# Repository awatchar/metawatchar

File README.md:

# metawatchar

Research repository for a PhD project on **electromagnetic metamaterials at RF frequencies**.

**Author:** Watchara Amasiri, Department of Electrical and Computer Engineering, Thammasat University

> Status: early stage, work in progress. Content will be added as the research progresses.

## Approach

The work combines simulation, fabrication, and measurement:

1. **Design and simulate** structures with open-source full-wave electromagnetic solvers, using an HPC cluster for parameter sweeps and optimization.
2. **Fabricate** prototypes as printed circuit boards.
3. **Measure** prototypes with RF instruments (vector network analysis, and free-space measurement in an anechoic chamber).
4. **Compare** measured and simulated results.

## Repository layout

| Path | Contents |
|---|---|
| `sim/<case>/` | Simulation scripts, job files, and summarized results (e.g., S-parameters, figures) for each case |

Large raw outputs, such as 3-D field dumps, are not stored in this repository.

## Reproducibility

Each case folder will describe the solver and version, the input parameters, and how to regenerate its results.

## License

- **Code** (scripts, simulation models, job files) is licensed under the [MIT License](LICENSE).
- **Data and results** (measured and simulated data, figures, and documentation) are licensed under [Creative Commons Attribution 4.0 International (CC BY 4.0)](LICENSE-CC-BY-4.0).

If you use this work, please cite the related publications (to be listed here) and credit Watchara Amasiri.

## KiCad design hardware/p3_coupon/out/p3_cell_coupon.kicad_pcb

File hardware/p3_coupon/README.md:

# P3 coupons and test fixtures (v1)

Boards for characterising the lumped LC cells of the 85 kHz magnetic metamaterial slab (study P3) before the slab itself is designed. All boards are generated by scripts (KiCad 10 Python) and checked by DRC: 0 errors, 0 warnings, no unconnected items.

| Board | Script | Size | Stack | Assembly | Purpose |
|---|---|---|---|---|---|
| `p3_cell_coupon` | `coupon_cells.py` | 225 × 210 mm | 2-layer, 1 oz | JLCPCB PCBA (81 parts) | Isolated cells (f0, Q, spread), coplanar pairs, L-only controls |
| `p3_array_coupon` | `coupon_arrays.py` | 270 × 185 mm | 2-layer, **2 oz** | JLCPCB PCBA (100 parts) + 1 hand-soldered SMA | 4 × 4 mini-arrays per cell type; printed-spiral reference cells |
| `p3_ztab` | `small_boards.py` | 11 × 52 mm | 2-layer, 1 oz | hand | One drum inductor + edge SMA: L, ESR, Q and Z21 vs distance (m_eff) |
| `p3_probe10`, `p3_probe20` | `small_boards.py` | 12 / 22 × 85 mm | **4-layer** | hand (SMA) | Shielded H-field loop probes, loop OD 10 / 20 mm |
| `p3_helmholtz` | `small_boards.py` | 110 × 110 mm | 2-layer, **2 oz** | hand (2 wires) | One coil of a Helmholtz pair for probe calibration |

Shared code: `p3pcb.py` (builder, cell types, spiral, export chain). Custom footprints: `footprints.pretty/`. Outputs: `out/` (boards, renders, DRC reports, cell maps) and `out/jlc_<board>/` (Gerber zip, BOM and CPL for JLCPCB).

## Cell types

Each cell is a closed loop: one unshielded ferrite drum inductor (axis normal to the board) and a C0G capacitor.

| Type | Inductor (LCSC) | Capacitor (LCSC) | Nominal f0 |
|---|---|---|---|
| A | Sumida CD105T125NP-470KC, 47 µH ±10 %, Ø10.4 mm (C171573) | Murata GRM3195C1H683JA05D, 68 nF C0G 1206 (C3847777) | 89.1 kHz |
| B | SXN SM7850-101MT, 100 µH ±20 %, Ø7.8 mm (C10155) | TDK C2012C0G1H333JT000N, 33 nF C0G 0805 (C76628) | 87.6 kHz |
| C | Bourns SDR0805-101KL, 100 µH ±10 %, Ø7.8 mm (C139487) | TDK C2012C0G1H333JT000N, 33 nF C0G 0805 (C76628) | 87.6 kHz |

Inductor footprints follow the manufacturers' recommended land patterns (Sumida CD105/T125 Ver. 2021-03-05; SXN SM series p. 2; Bourns SDR0805). The Z-tab uses one universal land that covers all three. The 3D bodies reuse KiCad's SDR1806 model scaled to size, for visualisation only.

## Board 1: cell coupon

- **Isolated cells A1–A7, B1–B7, C1–C7** at 30 mm pitch (neighbour coupling k ≲ 10⁻³, below 1/Q). Each has a DNP pad for a parallel trim capacitor.
- **Pairs xP11.5, xP14, xP18** (x = A, B, C): coplanar cells at 11.5, 14 and 18 mm centre spacing. The pair splits into two modes, and k = (f+² − f−²)/(f+² + f−²) where the splitting exceeds the linewidth. For coplanar cells k < 0.
- **AL, BL, CL**: inductor without a capacitor (the non-resonant control).
- Four M3 holes locate the 3D-printed probe jig. Cell coordinates are in `out/p3_cell_coupon_map.json`.

## Board 2: mini-arrays and printed reference cells

- **4 × 4 arrays**: type A at 15 mm pitch, B and C at 12.5 mm. The capacitor sits in the gap beside each inductor; there are no trim pads. These show the collective (uniform) mode of a small lattice, which is checked against the full mutual-inductance model.
- **S1, S2**: printed square spiral, 38 mm, 17 turns, 0.6 mm trace with 0.25 mm gap, top layer, bottom-layer crossover. L ≈ 7.7 µH (modified Wheeler), with 2 × 220 nF C0G (Murata GRM31C5C1H224JE02L, C464977) giving 86.7 kHz nominal, plus a DNP trim pad. Q is only about 6 at most, even with 2 oz copper. This is the exactly modelled reference cell, not a performance cell.
- **SZ**: the same spiral with no capacitor, wired to an edge SMA (J1, hand-soldered) for a direct measurement of L and R.

## Small boards

- **Z-tab**: the inductor sits at the tip (11 mm wide, so two tabs side by side reach 11.5 mm centre spacing) and the edge SMA at the far end. The feed is a top/bottom broadside pair, which keeps the lead loop small.
  - One tab gives L, ESR and Q.
  - Two tabs on the jig give Z21 = jωM against distance, which is fitted to M = μ0 m_eff² / (4π d³) for the coplanar case (and the coaxial case if stacked).
  - Order 10.
- **Loop probes**: two turns on each inner layer (four in series, OD 10 or 20 mm). Both outer layers are a ground shield, slit from the loop centre to the tip, so H passes, E is blocked, and the shield forms no shorted turn. Stitching vias run along the stem. The loop meets ground only at the connector, through a net tie.
  - The pair is used weakly coupled for cell f0/Q, and singly for field maps.
- **Helmholtz coil**: a 10-turn circular spiral, r = 46 → 34 mm (mean 40 mm). Two boards go on 40 mm spacers with the coils in series. The calibration field is computed from the actual track geometry (Biot–Savart), not from the ideal-loop formula.

## Ordering (one batch)

| Board | Qty | Options |
|---|---|---|
| Cell coupon | 5 PCB, 2 assembled | FR-4 1.6 mm, 1 oz, ENIG (flat lands for the large inductors), PCBA top side |
| Array coupon | 5 PCB, 2 assembled | FR-4 1.6 mm, **2 oz**, ENIG, PCBA top side |
| Z-tab | 10 | FR-4 1.6 mm, 1 oz |
| Probe 10, Probe 20 | 5 each | **4-layer**, 1.6 mm, standard stack-up |
| Helmholtz | 5 (2 needed) | FR-4 1.6 mm, **2 oz** |

**Loose parts for hand assembly:**
- Drum inductors of each type for the Z-tabs (about 4 of each).
- Edge-mount SMA jacks for 1.6 mm boards: 4 for the probes, 1 for SZ, and up to 10 for Z-tabs. The footprint is Samtec SMA-J-P-H-ST-EM1. Check that any generic edge SMA you buy matches its pads (centre 1.27 × 3.2 mm; grounds at ±2.825 mm, top and bottom).
- M3 nylon spacers, 40 mm, for the Helmholtz pair.

**Check in the JLCPCB DFM preview before paying:**
- Inductor rotation: both pads must lie along the board's y axis.
- The SDR0805 pad gap is read from the datasheet figure as 2.4 mm. Compare it with the library footprint of C139487.
- On the array coupon, the capacitor positions between the inductors.

## Regenerate

```bash
"C:/Program Files/KiCad/10.0/bin/python.exe" coupon_cells.py
```

Run `coupon_arrays.py` and `small_boards.py` the same way. Each script saves the board and then runs DRC, the Gerber/drill/position exports, the JLCPCB BOM/CPL and the renders.

## Not included yet

- The 3D-printed probe jig.
- TX/RX WPT coils and the slab itself. These are designed after the coupon data (cell Q, m_eff and spread) are measured.

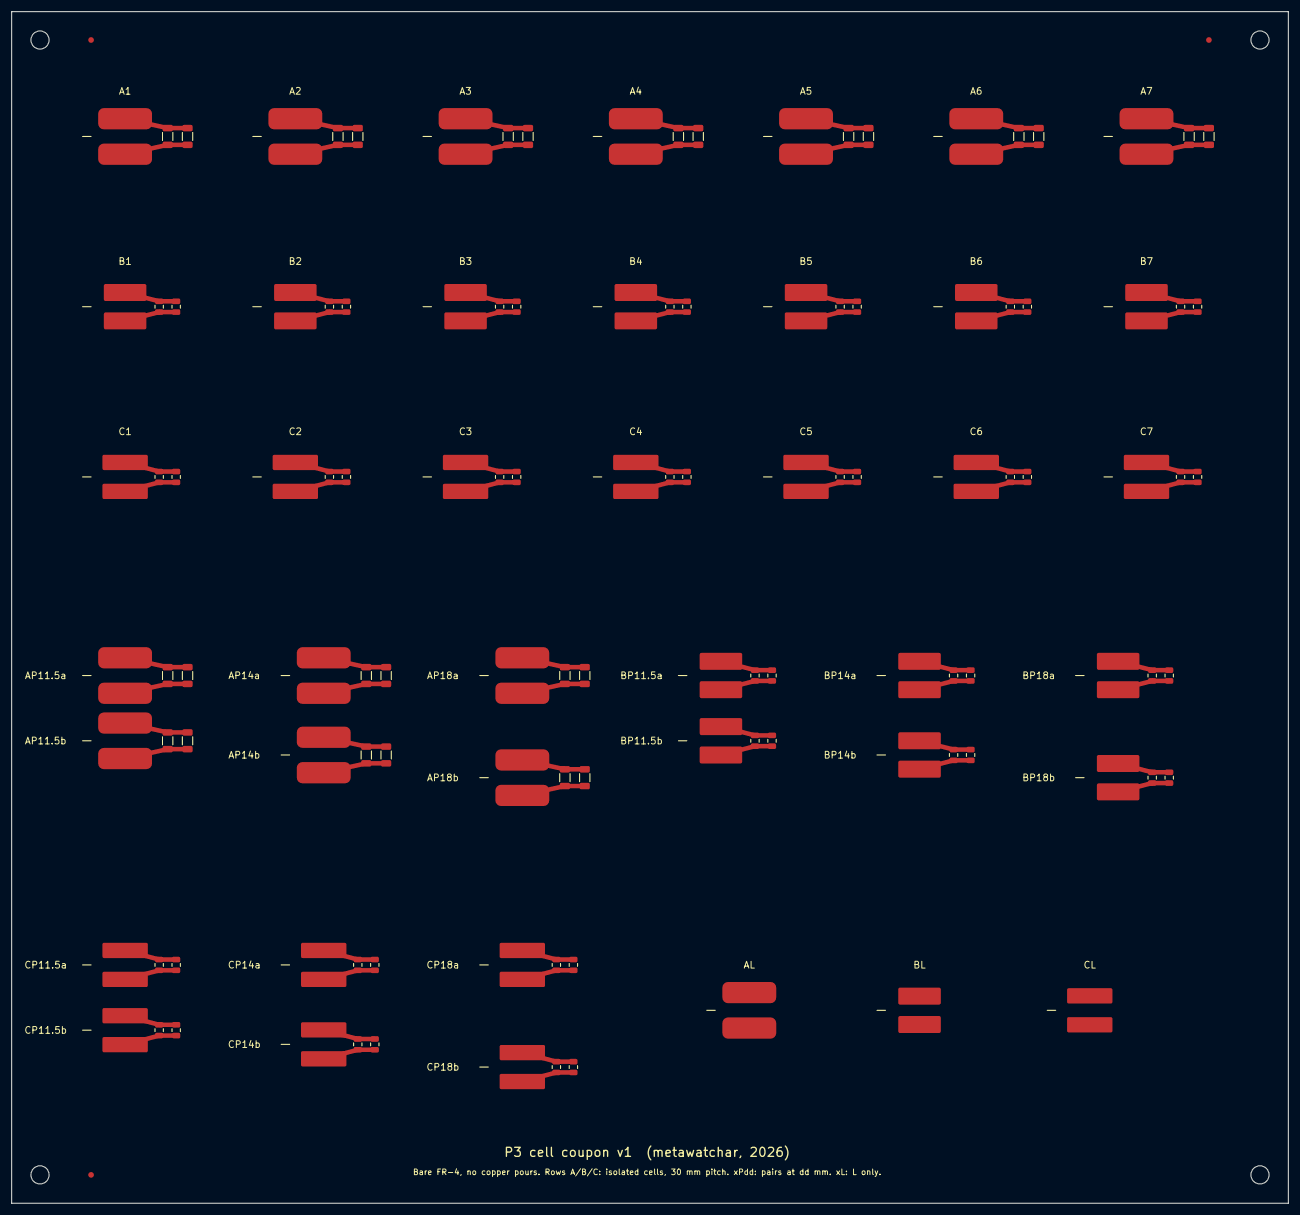
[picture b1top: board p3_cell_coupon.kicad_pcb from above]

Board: 2 copper layers, 225.0 x 210.0 mm, 127 parts (0 on the bottom side), 78 nets.

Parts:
C1, C3, C5, C7, C9, C11, C13, C43, C45, C47, C49, C51, C53: 68nF C0G; C_1206_3216Metric
C2, C4, C6, C8, C10, C12, C14, C44, C46, C48, C50, C52, C54: DNP trim; C_1206_3216Metric
C15, C17, C19, C21, C23, C25, C27, C29, C31, C33, C35, C37, C39, C41, C55, C57, C59, C61, C63, C65, C67, C69, C71, C73, C75, C77: 33nF C0G; C_0805_2012Metric
C16, C18, C20, C22, C24, C26, C28, C30, C32, C34, C36, C38, C40, C42, C56, C58, C60, C62, C64, C66, C68, C70, C72, C74, C76, C78: DNP trim; C_0805_2012Metric
FID1, FID2, FID3: Fiducial; Fiducial_1mm_Mask2mm
H1, H2, H3, H4: M3 jig hole; MountingHole_3.2mm_M3
L1, L2, L3, L4, L5, L6, L7, L22, L23, L24, L25, L26, L27, L40: 47uH; L_Sumida_CD105T125
L8, L9, L10, L11, L12, L13, L14, L28, L29, L30, L31, L32, L33, L41: 100uH; L_SXN_SM7850
L15, L16, L17, L18, L19, L20, L21, L34, L35, L36, L37, L38, L39, L42: 100uH; L_Bourns_SDR0805

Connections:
A1_a: C1.2, C2.2, L1.1
A1_b: C1.1, C2.1, L1.2
A2_a: C3.2, C4.2, L2.1
A2_b: C3.1, C4.1, L2.2
A3_a: C5.2, C6.2, L3.1
A3_b: C5.1, C6.1, L3.2
A4_a: C7.2, C8.2, L4.1
A4_b: C7.1, C8.1, L4.2
A5_a: C9.2, C10.2, L5.1
A5_b: C9.1, C10.1, L5.2
A6_a: C11.2, C12.2, L6.1
A6_b: C11.1, C12.1, L6.2
A7_a: C13.2, C14.2, L7.1
A7_b: C13.1, C14.1, L7.2
AP11.5a_a: C43.2, C44.2, L22.1
AP11.5a_b: C43.1, C44.1, L22.2
AP11.5b_a: C45.2, C46.2, L23.1
AP11.5b_b: C45.1, C46.1, L23.2
AP14a_a: C47.2, C48.2, L24.1
AP14a_b: C47.1, C48.1, L24.2
AP14b_a: C49.2, C50.2, L25.1
AP14b_b: C49.1, C50.1, L25.2
AP18a_a: C51.2, C52.2, L26.1
AP18a_b: C51.1, C52.1, L26.2
AP18b_a: C53.2, C54.2, L27.1
AP18b_b: C53.1, C54.1, L27.2
B1_a: C15.2, C16.2, L8.2
B1_b: C15.1, C16.1, L8.1
B2_a: C17.2, C18.2, L9.2
B2_b: C17.1, C18.1, L9.1
B3_a: C19.2, C20.2, L10.2
B3_b: C19.1, C20.1, L10.1
B4_a: C21.2, C22.2, L11.2
B4_b: C21.1, C22.1, L11.1
B5_a: C23.2, C24.2, L12.2
B5_b: C23.1, C24.1, L12.1
B6_a: C25.2, C26.2, L13.2
B6_b: C25.1, C26.1, L13.1
B7_a: C27.2, C28.2, L14.2
B7_b: C27.1, C28.1, L14.1
BP11.5a_a: C55.2, C56.2, L28.2
BP11.5a_b: C55.1, C56.1, L28.1
BP11.5b_a: C57.2, C58.2, L29.2
BP11.5b_b: C57.1, C58.1, L29.1
BP14a_a: C59.2, C60.2, L30.2
BP14a_b: C59.1, C60.1, L30.1
BP14b_a: C61.2, C62.2, L31.2
BP14b_b: C61.1, C62.1, L31.1
BP18a_a: C63.2, C64.2, L32.2
BP18a_b: C63.1, C64.1, L32.1
BP18b_a: C65.2, C66.2, L33.2
BP18b_b: C65.1, C66.1, L33.1
C1_a: C29.2, C30.2, L15.1
C1_b: C29.1, C30.1, L15.2
C2_a: C31.2, C32.2, L16.1
C2_b: C31.1, C32.1, L16.2
C3_a: C33.2, C34.2, L17.1
C3_b: C33.1, C34.1, L17.2
C4_a: C35.2, C36.2, L18.1
C4_b: C35.1, C36.1, L18.2
C5_a: C37.2, C38.2, L19.1
C5_b: C37.1, C38.1, L19.2
C6_a: C39.2, C40.2, L20.1
C6_b: C39.1, C40.1, L20.2
C7_a: C41.2, C42.2, L21.1
C7_b: C41.1, C42.1, L21.2
CP11.5a_a: C67.2, C68.2, L34.1
CP11.5a_b: C67.1, C68.1, L34.2
CP11.5b_a: C69.2, C70.2, L35.1
CP11.5b_b: C69.1, C70.1, L35.2
CP14a_a: C71.2, C72.2, L36.1
CP14a_b: C71.1, C72.1, L36.2
CP14b_a: C73.2, C74.2, L37.1
CP14b_b: C73.1, C74.1, L37.2
CP18a_a: C75.2, C76.2, L38.1
CP18a_b: C75.1, C76.1, L38.2
CP18b_a: C77.2, C78.2, L39.1
CP18b_b: C77.1, C78.1, L39.2

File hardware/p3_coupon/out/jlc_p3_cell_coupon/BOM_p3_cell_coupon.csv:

Comment,Designator,Footprint,LCSC Part #,Manufacturer Part,Qty
47uH,"L1,L2,L3,L4,L5,L6,L7,L22,L23,L24,L25,L26,L27,L40",L_Sumida_CD105T125,C171573,CD105T125NP-470KC,14
68nF C0G,"C1,C3,C5,C7,C9,C11,C13,C43,C45,C47,C49,C51,C53",C_1206_3216Metric,C3847777,GRM3195C1H683JA05D,13
100uH,"L8,L9,L10,L11,L12,L13,L14,L28,L29,L30,L31,L32,L33,L41",L_SXN_SM7850,C10155,SM7850-101MT,14
33nF C0G,"C15,C17,C19,C21,C23,C25,C27,C29,C31,C33,C35,C37,C39,C41,C55,C57,C59,C61,C63,C65,C67,C69,C71,C73,C75,C77",C_0805_2012Metric,C76628,C2012C0G1H333JT000N,26
100uH,"L15,L16,L17,L18,L19,L20,L21,L34,L35,L36,L37,L38,L39,L42",L_Bourns_SDR0805,C139487,SDR0805-101KL,14

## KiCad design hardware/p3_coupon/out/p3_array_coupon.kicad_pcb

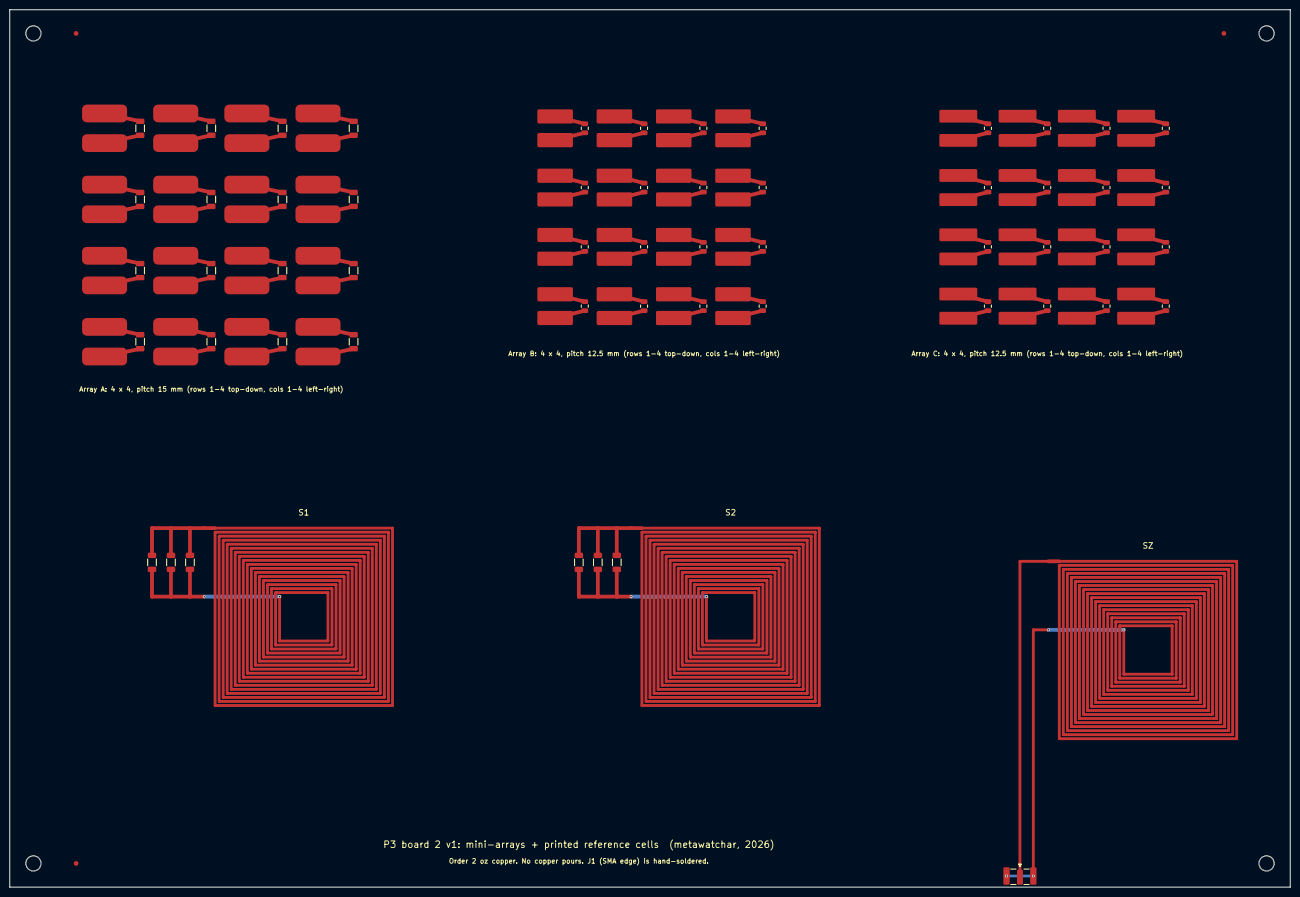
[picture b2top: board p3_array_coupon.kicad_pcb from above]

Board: 2 copper layers, 270.0 x 185.0 mm, 110 parts (0 on the bottom side), 99 nets.

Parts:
C1, C2, C3, C4, C5, C6, C7, C8, C9, C10, C11, C12, C13, C14, C15, C16: 68nF C0G; C_1206_3216Metric
C17, C18, C19, C20, C21, C22, C23, C24, C25, C26, C27, C28, C29, C30, C31, C32, C33, C34, C35, C36, C37, C38, C39, C40, C41, C42, C43, C44, C45, C46, C47, C48: 33nF C0G; C_0805_2012Metric
C49, C50, C52, C53: 220nF C0G; C_1206_3216Metric
C51, C54: DNP trim; C_1206_3216Metric
FID1, FID2, FID3: Fiducial; Fiducial_1mm_Mask2mm
H1, H2, H3, H4: M3 jig hole; MountingHole_3.2mm_M3
J1: SMA edge (hand solder); SMA_Samtec_SMA-J-P-H-ST-EM1_EdgeMount
L1, L2, L3, L4, L5, L6, L7, L8, L9, L10, L11, L12, L13, L14, L15, L16: 47uH; L_Sumida_CD105T125
L17, L18, L19, L20, L21, L22, L23, L24, L25, L26, L27, L28, L29, L30, L31, L32: 100uH; L_SXN_SM7850
L33, L34, L35, L36, L37, L38, L39, L40, L41, L42, L43, L44, L45, L46, L47, L48: 100uH; L_Bourns_SDR0805

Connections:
MA11_a: C1.2, L1.1
MA11_b: C1.1, L1.2
MA12_a: C5.2, L5.1
MA12_b: C5.1, L5.2
MA13_a: C9.2, L9.1
MA13_b: C9.1, L9.2
MA14_a: C13.2, L13.1
MA14_b: C13.1, L13.2
MA21_a: C2.2, L2.1
MA21_b: C2.1, L2.2
MA22_a: C6.2, L6.1
MA22_b: C6.1, L6.2
MA23_a: C10.2, L10.1
MA23_b: C10.1, L10.2
MA24_a: C14.2, L14.1
MA24_b: C14.1, L14.2
MA31_a: C3.2, L3.1
MA31_b: C3.1, L3.2
MA32_a: C7.2, L7.1
MA32_b: C7.1, L7.2
MA33_a: C11.2, L11.1
MA33_b: C11.1, L11.2
MA34_a: C15.2, L15.1
MA34_b: C15.1, L15.2
MA41_a: C4.2, L4.1
MA41_b: C4.1, L4.2
MA42_a: C8.2, L8.1
MA42_b: C8.1, L8.2
MA43_a: C12.2, L12.1
MA43_b: C12.1, L12.2
MA44_a: C16.2, L16.1
MA44_b: C16.1, L16.2
MB11_a: C17.2, L17.2
MB11_b: C17.1, L17.1
MB12_a: C21.2, L21.2
MB12_b: C21.1, L21.1
MB13_a: C25.2, L25.2
MB13_b: C25.1, L25.1
MB14_a: C29.2, L29.2
MB14_b: C29.1, L29.1
MB21_a: C18.2, L18.2
MB21_b: C18.1, L18.1
MB22_a: C22.2, L22.2
MB22_b: C22.1, L22.1
MB23_a: C26.2, L26.2
MB23_b: C26.1, L26.1
MB24_a: C30.2, L30.2
MB24_b: C30.1, L30.1
MB31_a: C19.2, L19.2
MB31_b: C19.1, L19.1
MB32_a: C23.2, L23.2
MB32_b: C23.1, L23.1
MB33_a: C27.2, L27.2
MB33_b: C27.1, L27.1
MB34_a: C31.2, L31.2
MB34_b: C31.1, L31.1
MB41_a: C20.2, L20.2
MB41_b: C20.1, L20.1
MB42_a: C24.2, L24.2
MB42_b: C24.1, L24.1
MB43_a: C28.2, L28.2
MB43_b: C28.1, L28.1
MB44_a: C32.2, L32.2
MB44_b: C32.1, L32.1
MC11_a: C33.2, L33.1
MC11_b: C33.1, L33.2
MC12_a: C37.2, L37.1
MC12_b: C37.1, L37.2
MC13_a: C41.2, L41.1
MC13_b: C41.1, L41.2
MC14_a: C45.2, L45.1
MC14_b: C45.1, L45.2
MC21_a: C34.2, L34.1
MC21_b: C34.1, L34.2
MC22_a: C38.2, L38.1
MC22_b: C38.1, L38.2
MC23_a: C42.2, L42.1
MC23_b: C42.1, L42.2
MC24_a: C46.2, L46.1
MC24_b: C46.1, L46.2
MC31_a: C35.2, L35.1
MC31_b: C35.1, L35.2
MC32_a: C39.2, L39.1
MC32_b: C39.1, L39.2
MC33_a: C43.2, L43.1
MC33_b: C43.1, L43.2
MC34_a: C47.2, L47.1
MC34_b: C47.1, L47.2
MC41_a: C36.2, L36.1
MC41_b: C36.1, L36.2
MC42_a: C40.2, L40.1
MC42_b: C40.1, L40.2
MC43_a: C44.2, L44.1
MC43_b: C44.1, L44.2
MC44_a: C48.2, L48.1
MC44_b: C48.1, L48.2
S1: C49.1, C49.2, C50.1, C50.2, C51.1, C51.2
S2: C52.1, C52.2, C53.1, C53.2, C54.1, C54.2
SZ: J1.1, J1.2

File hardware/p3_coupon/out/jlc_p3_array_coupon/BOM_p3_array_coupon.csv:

Comment,Designator,Footprint,LCSC Part #,Manufacturer Part,Qty
47uH,"L1,L2,L3,L4,L5,L6,L7,L8,L9,L10,L11,L12,L13,L14,L15,L16",L_Sumida_CD105T125,C171573,CD105T125NP-470KC,16
68nF C0G,"C1,C2,C3,C4,C5,C6,C7,C8,C9,C10,C11,C12,C13,C14,C15,C16",C_1206_3216Metric,C3847777,GRM3195C1H683JA05D,16
100uH,"L17,L18,L19,L20,L21,L22,L23,L24,L25,L26,L27,L28,L29,L30,L31,L32",L_SXN_SM7850,C10155,SM7850-101MT,16
33nF C0G,"C17,C18,C19,C20,C21,C22,C23,C24,C25,C26,C27,C28,C29,C30,C31,C32,C33,C34,C35,C36,C37,C38,C39,C40,C41,C42,C43,C44,C45,C46,C47,C48",C_0805_2012Metric,C76628,C2012C0G1H333JT000N,32
100uH,"L33,L34,L35,L36,L37,L38,L39,L40,L41,L42,L43,L44,L45,L46,L47,L48",L_Bourns_SDR0805,C139487,SDR0805-101KL,16
220nF C0G,"C49,C50,C52,C53",C_1206_3216Metric,C464977,GRM31C5C1H224JE02L,4
